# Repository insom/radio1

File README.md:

Radio #1
========

This is my very first PCB design. Against the odds, it's also functional
in its original state.

This board consists of two largely unrelated pieces:

* an 8x LED display driven by a 74HC374N octal D-type latch attached to the
  Raspberry Pi's GPIO pins.
* a radio receiver circuit, consisting of an ATmega168 or ATmega328 connected
  to the Raspberry Pi's UART and to a 433Mhz OOK/ASK radio.

(Why? Because I had 5x5cm to use up!)

License
-------

Copyright (c) 2014, Aaron Brady

Permission is hereby granted, free of charge, to any person obtaining a copy
of this software and associated documentation files (the "Software"), to deal
in the Software without restriction, including without limitation the rights
to use, copy, modify, merge, publish, distribute, sublicense, and/or sell
copies of the Software, and to permit persons to whom the Software is
furnished to do so, subject to the following conditions:

The above copyright notice and this permission notice shall be included in
all copies or substantial portions of the Software.

THE SOFTWARE IS PROVIDED "AS IS", WITHOUT WARRANTY OF ANY KIND, EXPRESS OR
IMPLIED, INCLUDING BUT NOT LIMITED TO THE WARRANTIES OF MERCHANTABILITY,
FITNESS FOR A PARTICULAR PURPOSE AND NONINFRINGEMENT. IN NO EVENT SHALL THE
AUTHORS OR COPYRIGHT HOLDERS BE LIABLE FOR ANY CLAIM, DAMAGES OR OTHER
LIABILITY, WHETHER IN AN ACTION OF CONTRACT, TORT OR OTHERWISE, ARISING FROM,
OUT OF OR IN CONNECTION WITH THE SOFTWARE OR THE USE OR OTHER DEALINGS IN
THE SOFTWARE.

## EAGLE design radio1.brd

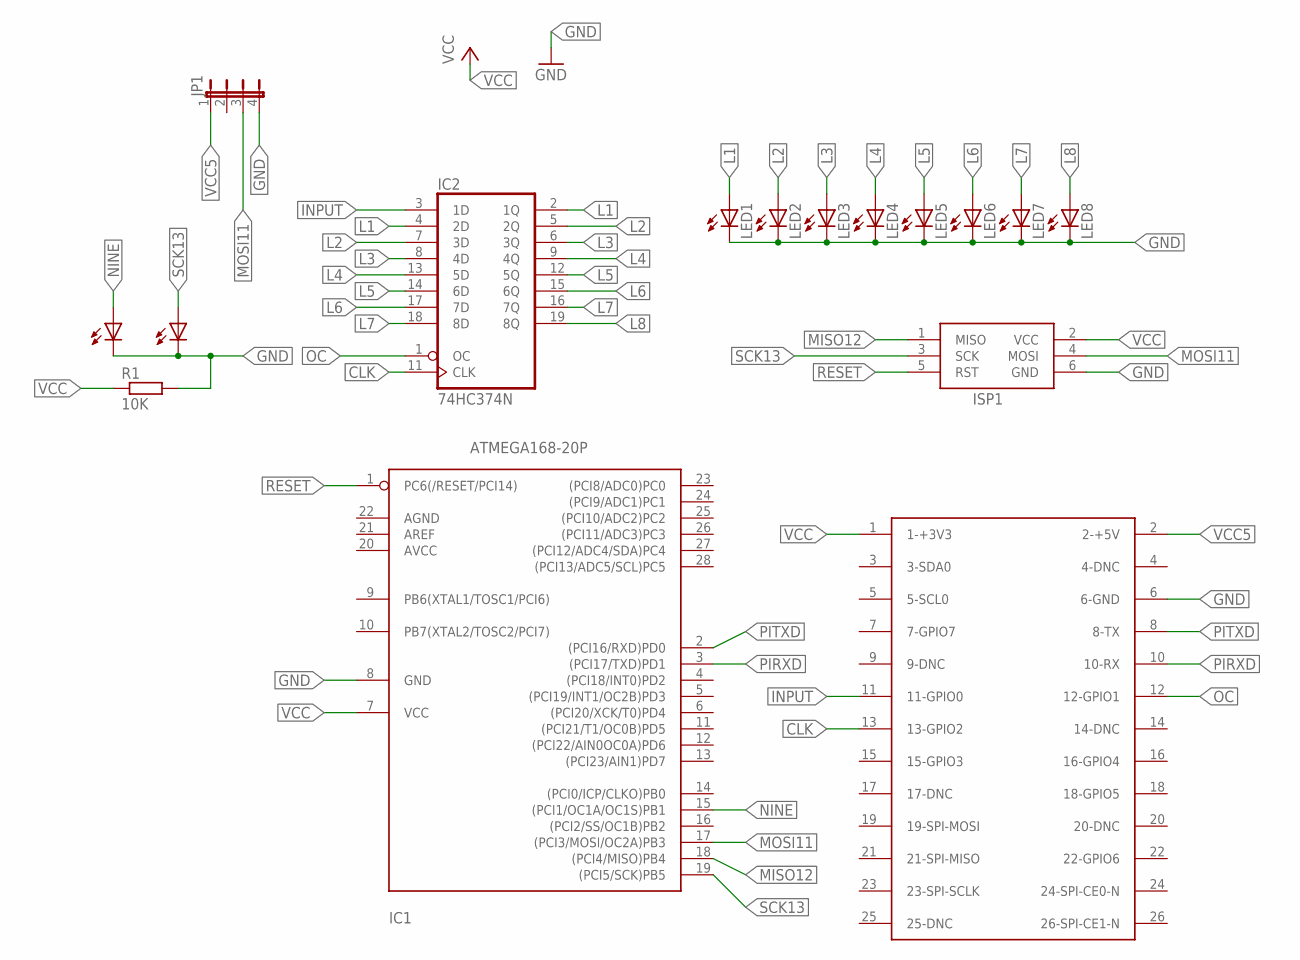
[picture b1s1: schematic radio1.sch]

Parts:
IC1: ATMEGA168-20P; DIL28-3
IC2: 74HC374N; DIL20
ISP1: AVRISP-6; AVRISP
JP1: JP4E; JP4
LED1, LED2, LED3, LED4, LED5, LED6, LED7, LED8, LED9, LED10: LED3MM
R1: 10K; 0204/7
U$1: RASPBERRY-PI

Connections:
CLK: IC2.11 (CLK), U$1.13 (13-GPIO2)
GND: IC1.8 (GND), IC2.10 (GND), ISP1.6 (GND), JP1.4, LED1.K (C), LED2.K (C), LED3.K (C), LED4.K (C), LED5.K (C), LED6.K (C), LED7.K (C), LED8.K (C), LED9.K (C), LED10.K (C), R1.2, U$1.6 (6-GND)
INPUT: IC2.3 (1D), U$1.11 (11-GPIO0)
L1: IC2.2 (1Q), IC2.4 (2D), LED1.A
L2: IC2.5 (2Q), IC2.7 (3D), LED2.A
L3: IC2.6 (3Q), IC2.8 (4D), LED3.A
L4: IC2.9 (4Q), IC2.13 (5D), LED4.A
L5: IC2.12 (5Q), IC2.14 (6D), LED5.A
L6: IC2.15 (6Q), IC2.17 (7D), LED6.A
L7: IC2.16 (7Q), IC2.18 (8D), LED7.A
L8: IC2.19 (8Q), LED8.A
MISO12: IC1.18 ((PCI4/MISO)PB4), ISP1.1 (MISO)
MOSI11: IC1.17 ((PCI3/MOSI/OC2A)PB3), ISP1.4 (MOSI), JP1.3
NINE: IC1.15 ((PCI1/OC1A/OC1S)PB1), LED9.A
OC: IC2.1 (OC), U$1.12 (12-GPIO1)
PIRXD: IC1.3 ((PCI17/TXD)PD1), U$1.10 (10-RX)
PITXD: IC1.2 ((PCI16/RXD)PD0), U$1.8 (8-TX)
RESET: IC1.1 (PC6(/RESET/PCI14)), ISP1.5 (RST)
SCK13: IC1.19 ((PCI5/SCK)PB5), ISP1.3 (SCK), LED10.A
VCC: IC1.7 (VCC), IC2.20 (VCC), ISP1.2 (VCC), R1.1, U$1.1 (1-+3V3)
VCC5: JP1.1, U$1.2 (2-+5V)

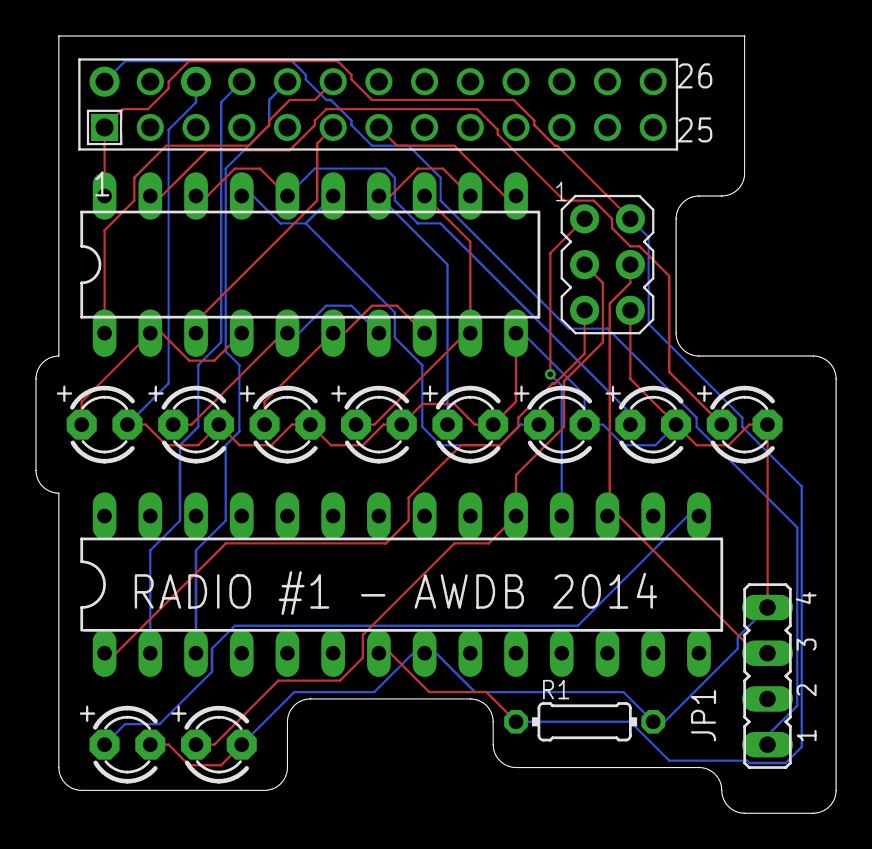
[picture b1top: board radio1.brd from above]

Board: 2 copper layers, 44.5 x 43.2 mm, 16 parts (0 on the bottom side), 21 nets.

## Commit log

2014-09-27 Add Arduino source
2014-09-28 Add custom board types, BusPirate programmer
2015-02-09 Better fuses for the 328P
